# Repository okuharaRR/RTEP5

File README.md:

# MyTea - The perfect cuppa, every time

Welcome to the MyTea github page - the tea making machine which brings you the perfect tea experience!

_A Raspberry PI will be used to control the entire process of tea preparation. Depending on the tea chosen by the user, the system will heat up water to the required temperature, dispense the required amount of tea leaves into a filter, infuse the leaves for a specified time, and finally pour the tea into a cup._

_With so many coffee machines available to satisfy every variety of coffee that anyone has ever came up with, this product aims to deliver the ultimate tea experience in an office environment or a public institution so that tea drinkers are not left at the mercy of the primitive old kettle..._

## Installation

On the terminal of a Raspberry Pi type the following:

```git clone https://github.com/okuharaRR/RTEP5.git```

```cd TeaMaker```

```qmake```

```make```

```./TeaMaker```

[Qt](https://www.qt.io/download) and [WiringPi](http://wiringpi.com/) are required.

If ```make``` gives an error, try ```make clean``` first and ```make```.

## Using the application

Once a finished product is made, using it will be straightforward:

1. Fill up the kettle with water and make sure the switch in the back is in the ON position. (_The need for a mechanical switch is for user safety_.)
2. Fill up the dispenser with tea leaves.
3. Once done, turn on the RPI and launch the GUI application.
4. Follow the guide [here](https://github.com/okuharaRR/RTEP5/wiki/User-Manual).

That's it!

## Demonstration

_Covid-19 has caused a significant distruption of our project and a complete demonstartor cannot be built to date. More information about the impact of the outbreak can be found [here](https://github.com/okuharaRR/RTEP5/wiki/Impact-of-Covid-19)._

A demonstration of the current state of the project can be found [here](https://www.youtube.com/watch?v=PhV0StMdRJc).

## Team Structure
* Boris Yanchev
   * hardware design, implementation and testing
   * mechanical design, procurement and manufacturing
   * GUI conceptual design
   * marketing
* Mika Okuhara
   * software development and documentation
   * hardware and software integration
   * test GUI implementation
* Muhammad Adeel Akram
   * marketing

## Further links

For further information about our project, have a look at our [Wiki](https://github.com/okuharaRR/RTEP5/wiki).

For software documentation, please click [here](https://okuhararr.github.io/RTEP5/).

You can find our website [here](https://rtesps.wixsite.com/mytea). 

Also, be sure to like our [Facebook page](https://www.facebook.com/MyTea-%E8%8C%B6-114110590136382/) and follow our [Twitter](https://twitter.com/MyTea76121892) to get all the latest updates!

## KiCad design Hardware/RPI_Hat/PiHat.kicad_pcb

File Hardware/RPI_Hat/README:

This folder contains the KiCad files for the PI hat for connections to the rest of the sub-modules.

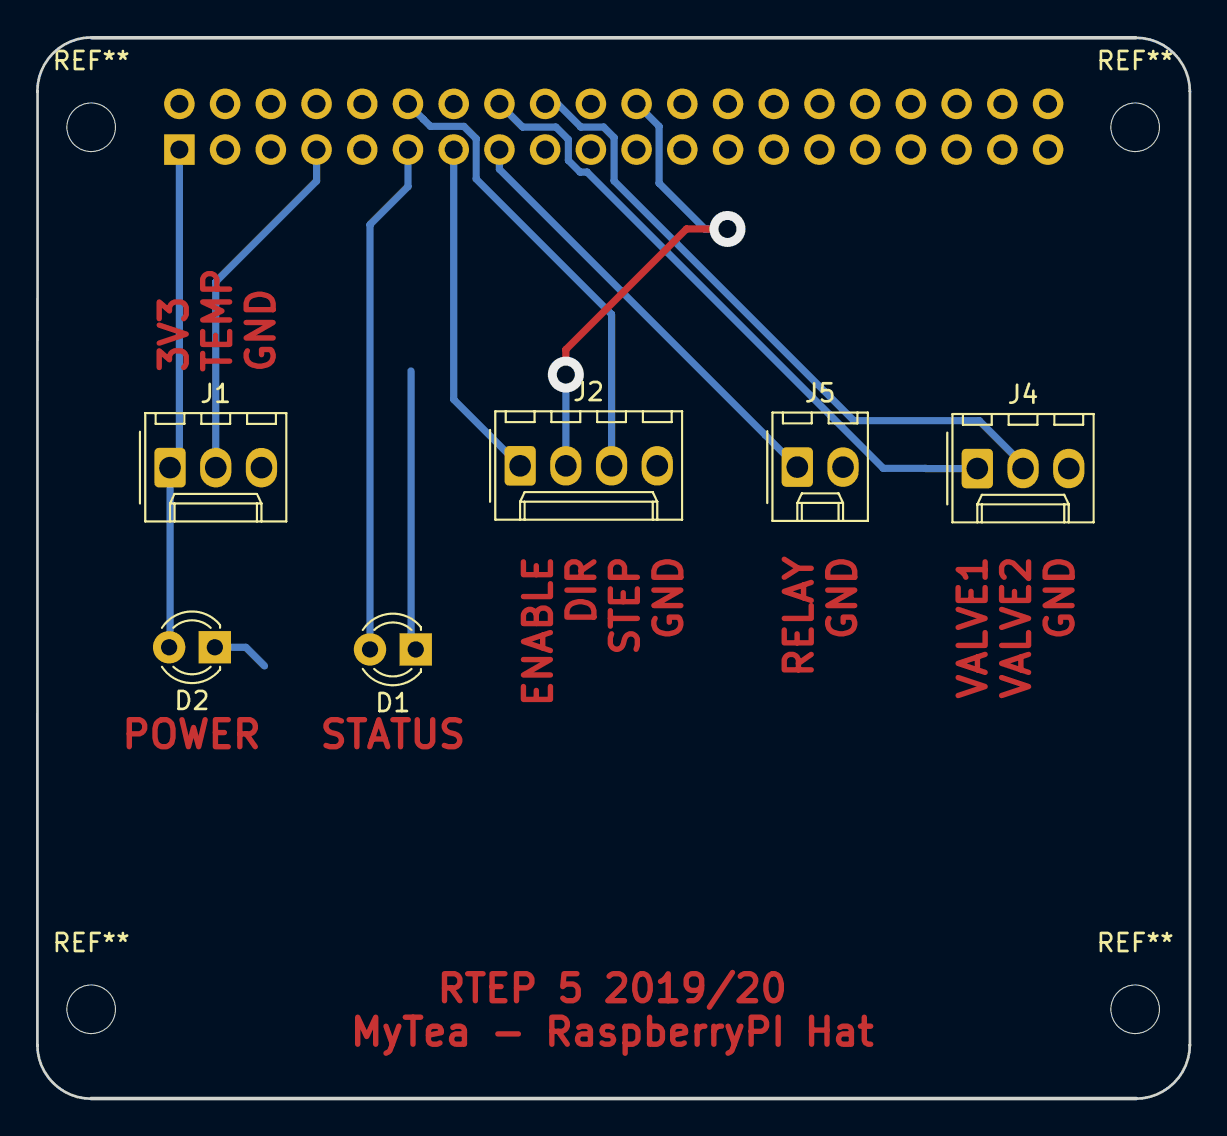
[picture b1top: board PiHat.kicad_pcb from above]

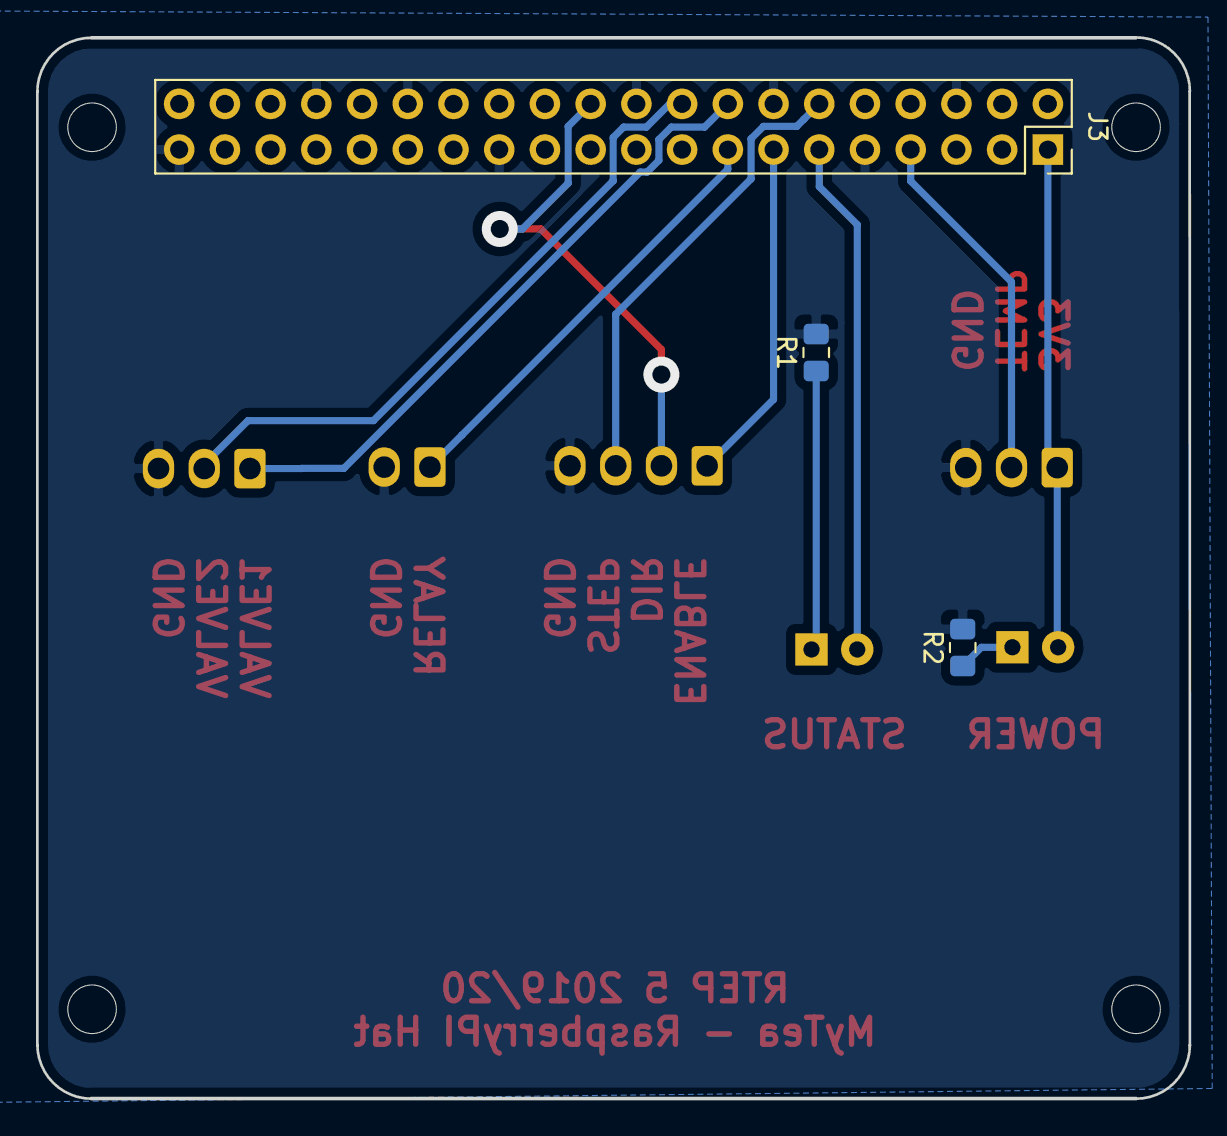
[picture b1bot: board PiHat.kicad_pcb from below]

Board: 2 copper layers, 64.0 x 58.9 mm, 9 parts (3 on the bottom side), 12 nets.

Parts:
D1, D2: LED; LED_D3.0mm
J1, J4: Conn_01x03; Molex_KK-254_AE-6410-03A_1x03_P2.54mm_Vertical
J2: Conn_01x04; Molex_KK-254_AE-6410-04A_1x04_P2.54mm_Vertical
J3: Conn_02x20_Odd_Even; PinSocket_2x20_P2.54mm_Vertical
J5: Conn_01x02; Molex_KK-254_AE-6410-02A_1x02_P2.54mm_Vertical
R1, R2: R; R_0805_2012Metric_Pad1.15x1.40mm_HandSolder

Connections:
3V3: D2.2, J1.1, J3.1
DIR: J2.2, J3.22
ENABLE: J2.1, J3.13
GND: J1.3, J2.4, J3.6, J3.9, J3.14, J3.20, J3.25, J3.30, J3.34, J3.39, J4.3, J5.2, R1.2, R2.2
unnamed: D1.1, R1.1
unnamed: D2.1, R2.1
RELAY: J3.15, J5.1
STATUS_LED: D1.2, J3.11
STEP: J2.3, J3.12
TEMP_SENSE: J1.2, J3.7
VALVE1: J3.16, J4.1
VALVE2: J3.18, J4.2

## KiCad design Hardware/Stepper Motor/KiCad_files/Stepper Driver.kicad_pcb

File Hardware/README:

*** RTEP5 MyTea Hardware ReadMe File ***

Each subfolder contains the layout masks, schematics, and BOMs for each PCB used in the project.

The layout masks can be used directly for PCB fabrication. 

The interactive BOMs, when opened with an internet browser, can be used to see individual component placement and track the population of components.

Similarly, the text BOMs show all components used in text form.

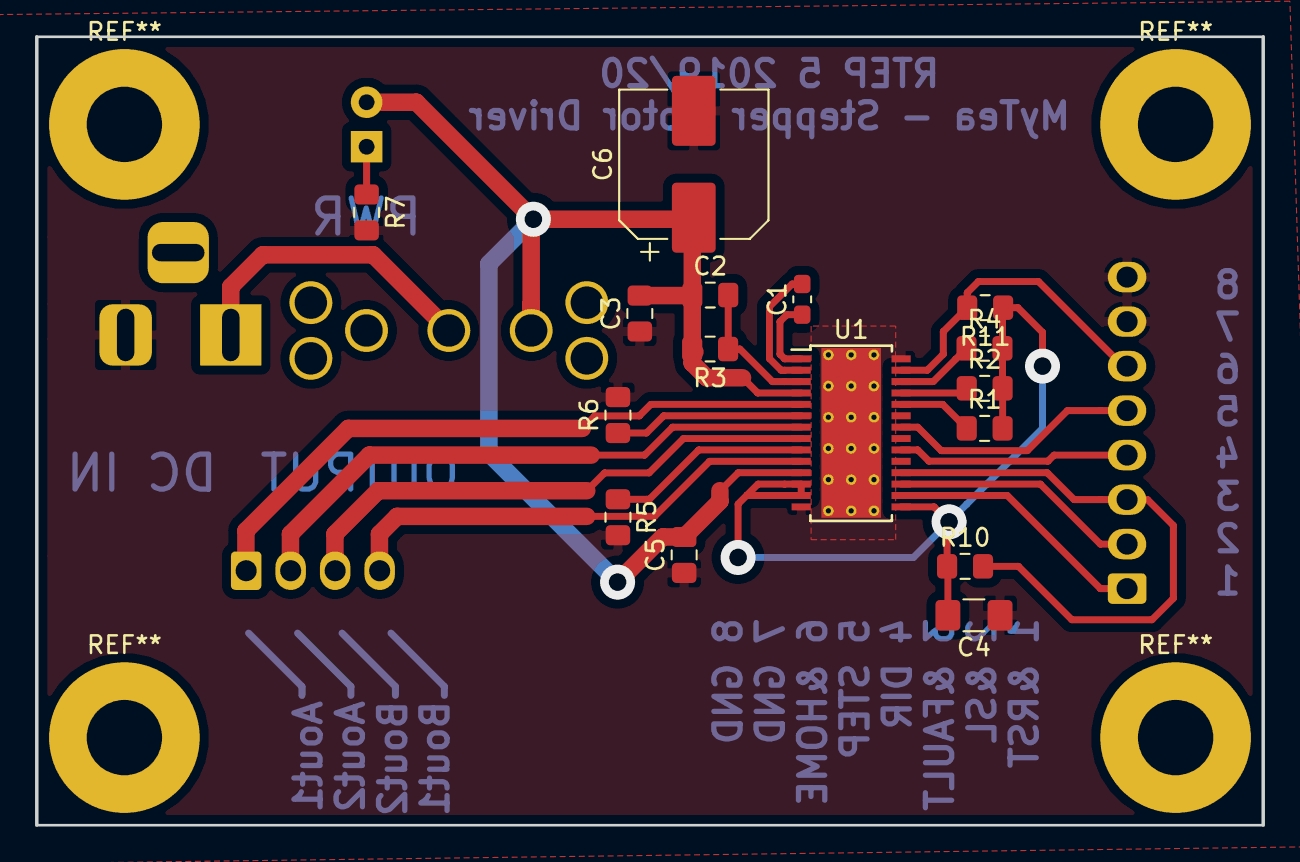
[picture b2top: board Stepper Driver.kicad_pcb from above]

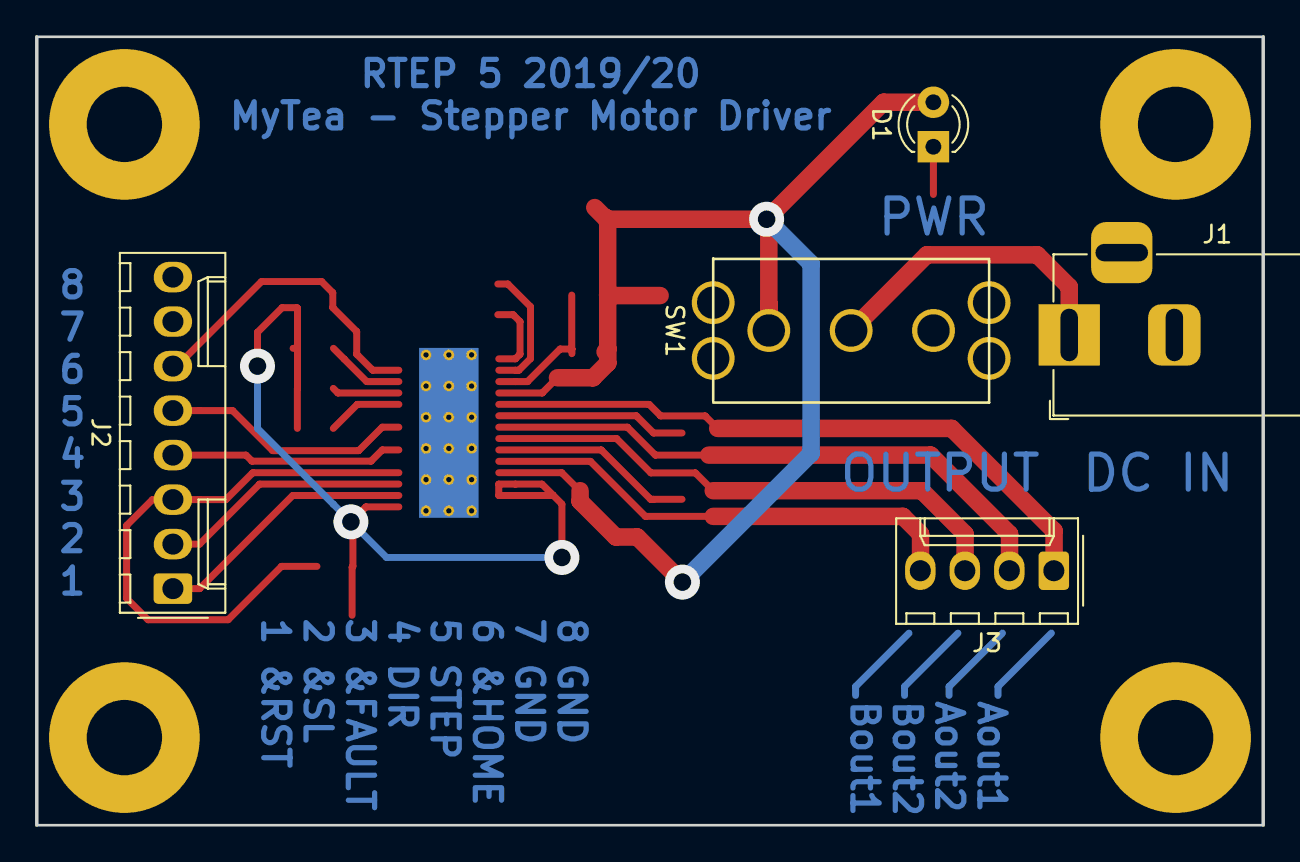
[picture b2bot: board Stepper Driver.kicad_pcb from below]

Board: 2 copper layers, 70.0 x 45.0 mm, 21 parts (5 on the bottom side), 23 nets.

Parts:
C1: 0.01u; C_0603_1608Metric_Pad1.05x0.95mm_HandSolder
C2, C3, C5: 0.1u; C_0805_2012Metric_Pad1.15x1.40mm_HandSolder
C4: 0.47u; C_1206_3216Metric_Pad1.42x1.75mm_HandSolder
C6: 100u; CP_Elec_8x5.4
D1: LED; LED_D3.0mm
J1: Jack-DC; BarrelJack_Horizontal
J2: Conn_01x08_Male; Molex_KK-254_AE-6410-08A_1x08_P2.54mm_Vertical
J3: Conn_01x04_Male; Molex_KK-254_AE-6410-04A_1x04_P2.54mm_Vertical
R1, R2, R4, R10, R11: 10k; R_0805_2012Metric_Pad1.15x1.40mm_HandSolder
R3: 1M; R_0805_2012Metric_Pad1.15x1.40mm_HandSolder
R5: Rsense_a; R_0805_2012Metric_Pad1.15x1.40mm_HandSolder
R6: Rsense_b; R_0805_2012Metric_Pad1.15x1.40mm_HandSolder
R7: Rled; R_0805_2012Metric_Pad1.15x1.40mm_HandSolder
SW1: SW_SPDT; SPDT_RockerSwitch
U1: DRV8825PWP; HTSSOP-28-1EP_4.4x9.7mm_P0.65mm_EP3.4x9.5mm_Mask2.4x6.17mm_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

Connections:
&FAULT: J2.3, R10.2, U1.18
&HOME: J2.6, R11.2, U1.27
&RST: J2.1, U1.16
&SL: J2.2, U1.17
AOUT1: J3.1, U1.5
AOUT2: J3.2, U1.7
BOUT1: J3.4, U1.10
BOUT2: J3.3, U1.8
DIR: J2.4, U1.20
GND: C3.1, C4.1, C5.1, C6.2, J1.2, J2.7, J2.8, R5.2, R6.2, R7.2, U1.14, U1.28, U1.29
unnamed: C1.1, U1.1
unnamed: C1.2, U1.2
unnamed: C2.2, R3.1, U1.3
unnamed: D1.1, R7.1
unnamed: J1.1, SW1.2
unnamed: R1.1, U1.24
unnamed: R2.1, U1.25
unnamed: R4.1, U1.26
unnamed: R5.1, U1.9
unnamed: R6.1, U1.6
STEP: J2.5, U1.22
VMOTOR: C2.1, C3.2, C5.2, C6.1, D1.2, R3.2, SW1.1, U1.4, U1.11
Vref: C4.2, R1.2, R2.2, R4.2, R10.1, R11.1, U1.12, U1.13, U1.15

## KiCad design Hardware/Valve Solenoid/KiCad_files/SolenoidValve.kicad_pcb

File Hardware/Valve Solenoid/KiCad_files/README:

KiCad files for the solenoid valve sub-module can be found here.

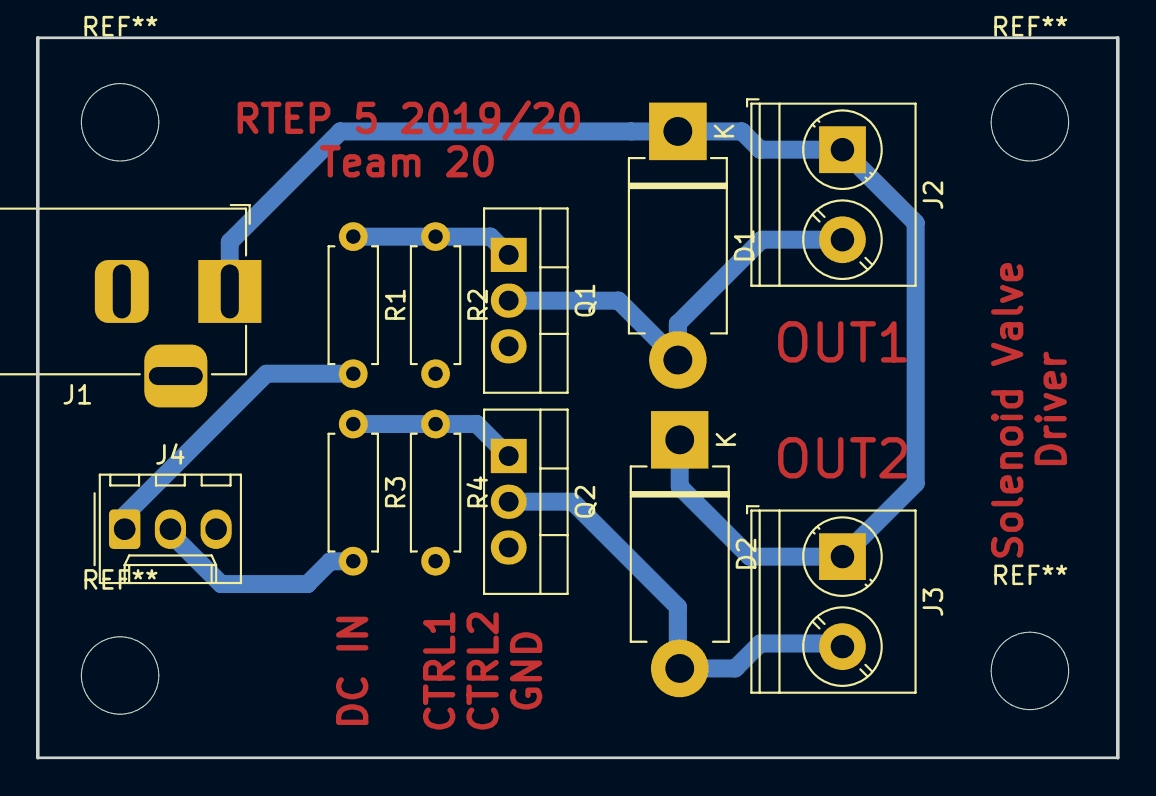
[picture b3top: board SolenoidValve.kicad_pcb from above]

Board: 2 copper layers, 60.0 x 40.0 mm, 12 parts (0 on the bottom side), 8 nets.

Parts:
D1, D2: D_Schottky; D_DO-201AD_P12.70mm_Horizontal
J1: Barrel_Jack; BarrelJack_Horizontal
J2, J3: Conn_01x02; TerminalBlock_Phoenix_PT-1,5-2-5.0-H_1x02_P5.00mm_Horizontal
J4: Conn_01x03; Molex_KK-254_AE-6410-03A_1x03_P2.54mm_Vertical
Q1, Q2: Q_NMOS_GDS; TO-220-3_Vertical
R1, R3: 1K; R_Axial_DIN0207_L6.3mm_D2.5mm_P7.62mm_Horizontal
R2, R4: 10K; R_Axial_DIN0207_L6.3mm_D2.5mm_P7.62mm_Horizontal

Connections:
+12V: D1.1, D2.1, J1.1, J2.1, J3.1
CTRL1: J4.1, R1.2
CTRL2: J4.2, R3.2
GND: J1.2, J4.3, Q1.3, Q2.3, R2.2, R4.2
unnamed: D1.2, J2.2, Q1.2
unnamed: D2.2, J3.2, Q2.2
unnamed: Q1.1, R1.1, R2.1
unnamed: Q2.1, R3.1, R4.1

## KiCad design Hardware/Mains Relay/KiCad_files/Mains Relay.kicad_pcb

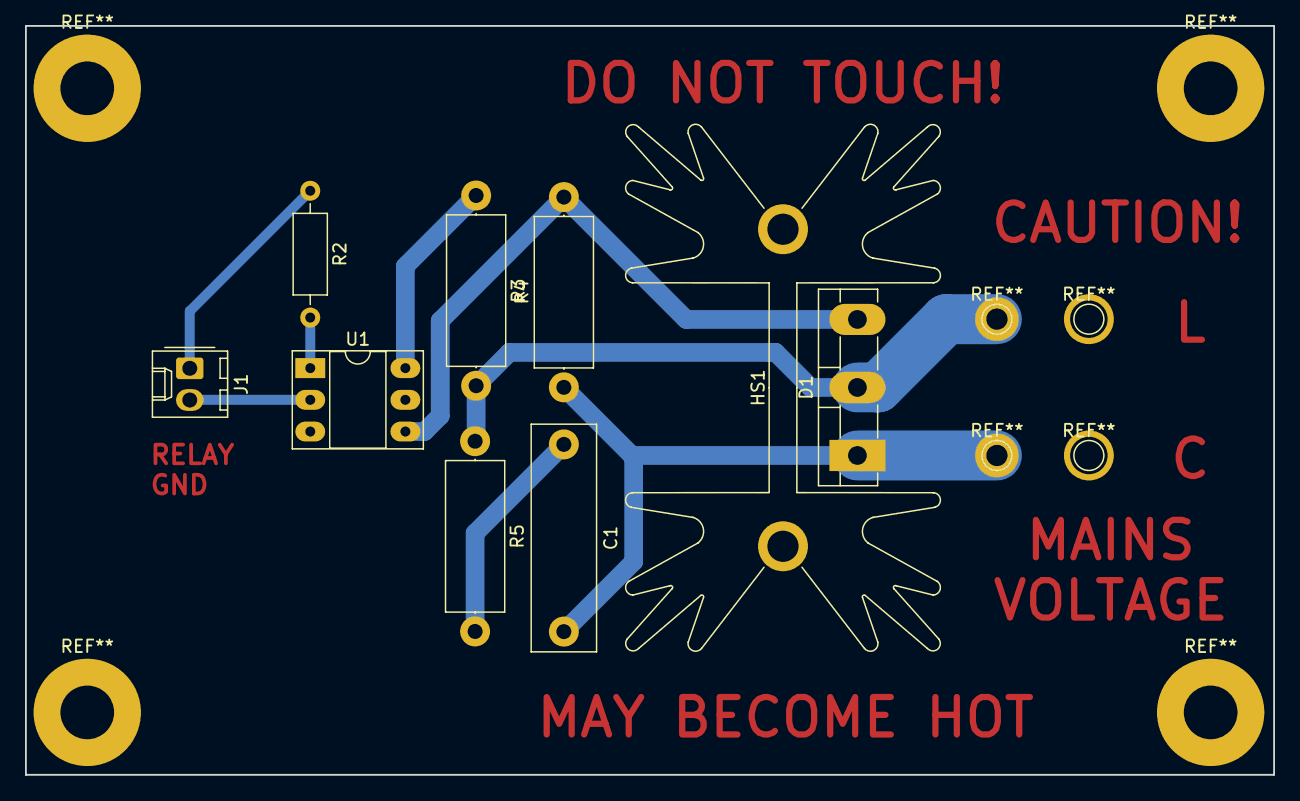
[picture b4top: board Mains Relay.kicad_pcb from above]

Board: 2 copper layers, 100.0 x 60.0 mm, 9 parts (0 on the bottom side), 8 nets.

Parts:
C1: 0.01u; C_Rect_L18.0mm_W5.0mm_P15.00mm_FKS3_FKP3
D1: Q_TRIAC_A1A2G; TO-3P-3_Vertical
HS1: Heatsink; Heatsink_Fischer_SK129-STS_42x25mm_2xDrill2.5mm
J1: Conn_01x02_Male; Molex_KK-254_AE-6410-02A_1x02_P2.54mm_Vertical
R2: 120; R_Axial_DIN0207_L6.3mm_D2.5mm_P10.16mm_Horizontal
R3: 360; R_Axial_DIN0414_L11.9mm_D4.5mm_P15.24mm_Horizontal
R4: 330; R_Axial_DIN0414_L11.9mm_D4.5mm_P15.24mm_Horizontal
R5: 39; R_Axial_DIN0414_L11.9mm_D4.5mm_P15.24mm_Horizontal
U1: MOC3061M; DIP-6_W7.62mm_Socket_LongPads

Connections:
CONTROL: C1.2, D1.1, R4.1
LIVE: D1.2, R3.2, R5.1
unnamed: C1.1, R5.2
unnamed: D1.3, R4.2, U1.4
unnamed: J1.1, R2.1
unnamed: J1.2, U1.2
unnamed: R2.2, U1.1
unnamed: R3.1, U1.6

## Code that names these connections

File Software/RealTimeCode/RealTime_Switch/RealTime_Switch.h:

#pragma once

#ifndef SWITCH_H
#define SWITCH_H

#include "CppTimer.h"


class Relay : public CppTimer {

public:

	void on();
	
	void timerEvent();
	
private:

	int relay = 3;            // GPIO pin for Relay

};
	
class Valve1 : public CppTimer {
	
 public:
 
	void on();
	
	void timerEvent();
	
private:

	int valve1 = 4;           // GPIO pi for valve 1
};
	
class Valve2 : public CppTimer {

 public:
 
	void on();
	
	void timerEvent();
	
 private:
	
	int valve2 = 5;
};

#endif 

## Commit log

2020-01-26 MyTea logo added
2020-01-26 Initial pitch presentation added
2020-01-26 Design concept diagram added
2020-01-28 DesignConcept.pdf moved to Wiki
2020-01-28 Moved to Wiki
2020-01-28 Updated README file
2020-01-29 this is my first commit
2020-01-29 removed the message
2020-01-29 Fixed typos in README
2020-02-04 Class_Diagram.jpg
2020-02-04 Software structure
2020-02-04 Changed Name
2020-02-04 Version 2
2020-02-04 New diagram was updated
2020-02-04 Version 3 software structure.jpg
2020-02-04 New diagram is updated
2020-02-04 Added Use Cases.jpg
2020-02-05 User stories initial commit
2020-02-05 Initial GUI concept commit
2020-02-18 Created mains relay verification procedure
2020-02-18 Added functional testing scope traces
2020-02-18 Updated and expanded document
2020-02-18 Added schematic and layer masks
2020-02-18 sample code for blinking LED
2020-02-20 Uploaded stepper motor driver masks
2020-02-20 Added IRL530 Spice model
2020-02-20 Basic example of class and inheritance
2020-02-20 Moved IRL530 model to correct folder
2020-02-20 Uploaded solenoid valve layer masks
2020-02-22 moved class diagrams to Class directory
2020-02-22 do not include space in file name
2020-02-22 changed name to remove spaces
2020-02-24 IRL530 model moved to correct folder
2020-02-24 Uploaded stepper driver schematic
2020-02-24 Uploaded stepper driver interactive BOM
2020-02-24 Created hardware readme file
2020-02-24 Uploaded stepper driver BOM
2020-02-26 Fixed LED not blinking
2020-02-26 Create LICENSE
2020-02-26 Stepper motor test code initial release
2020-03-02 test code directory
2020-03-02 test codes moved to test directory
2020-03-03 Motor test code done
2020-03-03 Sensor test code done
2020-03-03 Switch test code done
2020-03-03 moved initial code to SourceCode directory
2020-03-03 simple test code for Qt
2020-03-09 Real_time sensor
2020-03-10 Create README for mains relay
2020-03-10 Added KiCad files for mains relay
2020-03-10 Add KiCad files
2020-03-10 Add KiCad files for solenoid valve
2020-03-10 Create README for mechanical design
2020-03-10 Add mechanical drawing for enclosure
2020-03-10 Motor runs in a thread
2020-03-11 Switch is implemented in real time
2020-03-11 "build" was added
2020-03-11 fix previous push
2020-03-11 Add SOLIDWORKS models
2020-03-11 upload Qt_test again
2020-03-12 Real Time sensor was implemented in .h and .cpp files
2020-03-12 Real Time motor is implemented with cppThread
2020-03-12 motor test done
2020-03-12 fixed bug in Real Time switch
2020-03-13 Real Time Sensor is implemented
2020-03-16 Add KiCad files for RPI hat
2020-03-16 motor rotation became bidirectional
2020-03-16 clockwise variable is used to change direction of rotation
2020-03-16 initial Qt with relay switch
2020-03-16 fixed links between source files
2020-03-16 save local changes to Qt files
2020-03-19 fixed the error when compiling cppTimer
2020-03-19 Real Time Switch 2 file was modified
2020-03-19 Real Time Switch 2 repository is cleaned up
2020-03-19 The error compiling cppTimer is fixed
2020-04-12 All switches were implememted
2020-04-12 A bug was fixed
2020-04-12 Sensor was implemnted in Qt
2020-04-12 modified CppTimer mode
2020-04-12 modified LED function in Sensor
2020-04-12 Motor is implemnted in Qt
2020-04-12 implementation completed
2020-04-12 Create readme for old docs folder
2020-04-12 Create C Basics
2020-04-12 testing QT code
2020-04-12 Rename C_Basics to C_Basics.md
2020-04-12 Add initial design concept
2020-04-12 Add pitch presentation
2020-04-12 Doxygen link is updated
2020-04-13 Rename README to README.md
2020-04-13 Move image to correct directory
2020-04-13 Doxygen links were added
2020-04-13 Add overall diagram
2020-04-13 files were cleaned up
2020-04-13 files and directories were cleaned up
2020-04-13 Add mains relay BoM
2020-04-13 Add mains relay interactive BoM
2020-04-13 Add solenoid valve schem and BoM
2020-04-13 Add valve solenoid interactive BoM
2020-04-13 Add PI hat BoM and interactive BoM
2020-04-13 Add PI hat PCB layer masks
2020-04-13 Add PiHat image
2020-04-13 Add stepper driver image
2020-04-13 Add assembly drawing
2020-04-13 Add dispenser image
2020-04-13 Add assembly models
2020-04-14 Update diagram
2020-04-14 Add PI hat schematic
2020-04-14 Fixed class diagram not opening
2020-04-14 Add user stories
2020-04-14 Add logo
2020-04-15 added .png extension
2020-04-15 Add early logo design
2020-04-15 Add GUI concept screens
2020-04-16 add doxygen docs (gh-pages)
2020-04-16 changed name to docs
2020-04-16 added doxygen html
2020-04-16 deleted docs/
2020-04-16 renamed html to docs
2020-04-16 Add links
2020-04-16 Add Gantt chart
2020-04-16 Update Gantt chart
2020-04-17 added changes to TeaMaker
2020-04-17 Updated TeaMaker
2020-04-19 Deleted RealTime_Switch2
2020-04-19 Updated RealTime_Sensor
2020-04-19 modified RealTime_Switch
2020-04-19 deleted unneccesary files
